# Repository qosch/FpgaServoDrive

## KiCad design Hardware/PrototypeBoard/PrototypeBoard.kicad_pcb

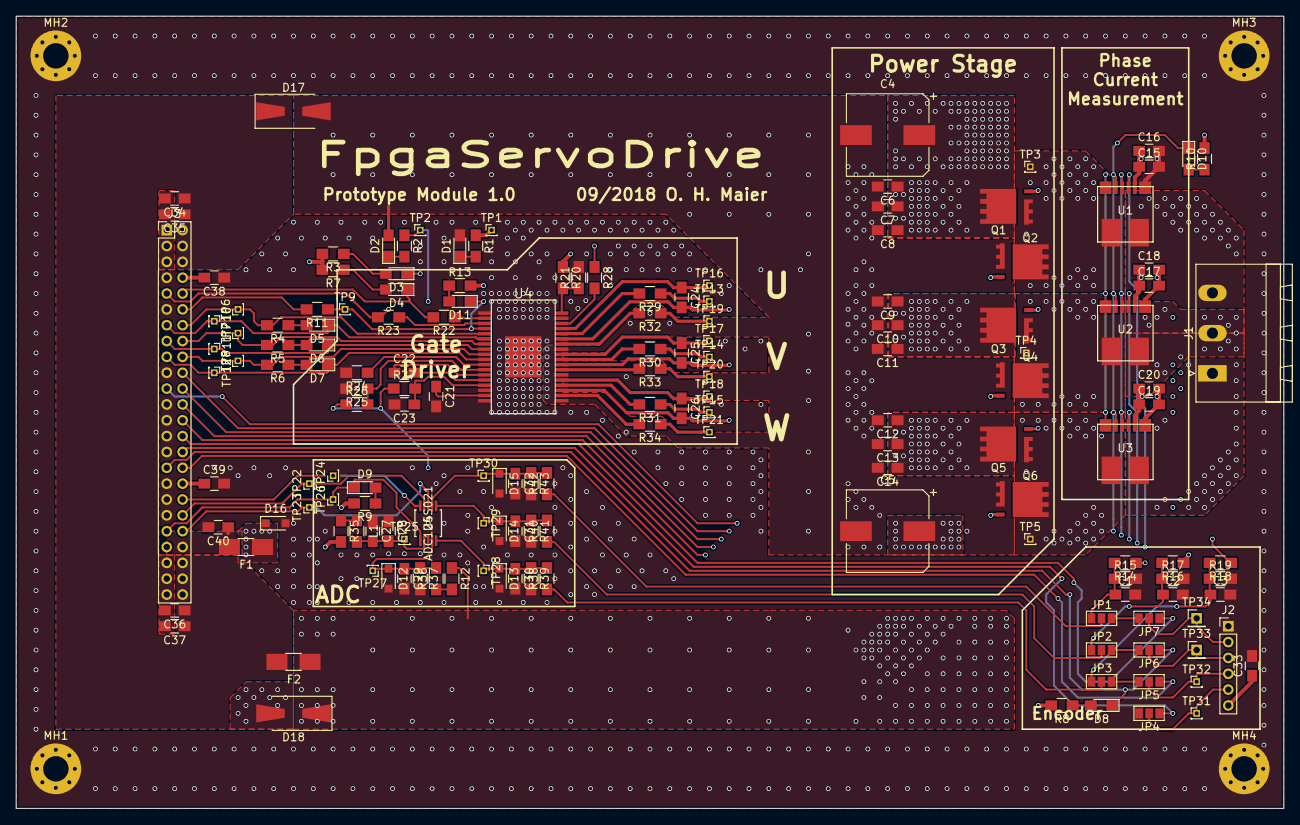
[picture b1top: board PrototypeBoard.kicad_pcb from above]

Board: 4 copper layers, 160.0 x 100.0 mm, 163 parts (0 on the bottom side), 91 nets.

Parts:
C1, C2, C3, C6, C8, C9, C11, C12, C14, C15, C17, C19, C28, C29, C33, C35, C36, C38, C39, C40: 100n; C_0805_HandSoldering
C4, C5: 220μF, 50V; CP_Elec_10x10
C7, C10, C13: 4.7μ, 50V; C_0805_HandSoldering
C16, C18, C20, C27: 1μ; C_0805_HandSoldering
C21, C23: 2,2µ; C_0805_HandSoldering
C22, C24, C25, C26: 1µ; C_0805_HandSoldering
C30, C31, C32: DNP; C_0805_HandSoldering
C34, C37: 4.7μ; C_0805_HandSoldering
D1: 3.3V; LED_0805_HandSoldering
D2: 5.5-28V; LED_0805_HandSoldering
D3, D4, D11: Red; LED_0805_HandSoldering
D5, D6, D7, D8, D9, D10: Yellow; LED_0805_HandSoldering
D12, D13, D14, D15: 3.3V; D_SOD-323_HandSoldering
D16: 3.5V; D_SOD-323_HandSoldering
D17, D18: 30V; D_SMA-SMB_Universal_Handsoldering
F1: 200mA; Fuse_SMD1206_HandSoldering
F2: 3A; Fuse_SMD1206_HandSoldering
J1: Conn_01x03; PhoenixContact_MSTBA-G_03x5.08mm_Angled
J2: Conn_01x06; Pin_Header_Straight_1x06_Pitch2.00mm
J3: ControlSupplyConnector; Pin_Header_Straight_2x24_Pitch2.00mm
JP1, JP2, JP3: Hall/Phase; GS3
JP4, JP5, JP6, JP7: SPI/Hall; GS3
L1: 1μ; L_0805_HandSoldering
MH1, MH2, MH3, MH4: MountingHole_Pad; MountingHole_3.2mm_M3_Pad_Via
Q1, Q2, Q3, Q4, Q5, Q6: Q_NMOS_SGD; TDSON-8_FL
R1, R3, R7, R13: 220; R_0805_HandSoldering
R2, R38, R40, R42: 6.8k; R_0805_HandSoldering
R4, R5, R6, R8, R9, R10: 560; R_0805_HandSoldering
R11, R21: 10k; R_0805_HandSoldering
R12, R24, R35: 0; R_0805_HandSoldering
R14, R16, R18: 1.5k; R_0805_HandSoldering
R15, R17, R19, R43: DNP; R_0805_HandSoldering
R20: 63k; R_0805_HandSoldering
R22, R23, R26: 5k; R_0805_HandSoldering
R25: 47k; R_0805_HandSoldering
R27: 4.7; R_0805_HandSoldering
R28, R37, R39, R41: 1k; R_0805_HandSoldering
R29, R30, R31, R32, R33, R34: 10; R_0805_HandSoldering
R36: 8.2k; R_0805_HandSoldering
TP1: 3.3V; Pin_Header_Straight_1x01_Pitch1.00mm
TP2: 5.5-28V; Pin_Header_Straight_1x01_Pitch1.00mm
TP3: PhaseU; Pin_Header_Straight_1x01_Pitch1.00mm
TP4: PhaseV; Pin_Header_Straight_1x01_Pitch1.00mm
TP5: PhaseW; Pin_Header_Straight_1x01_Pitch1.00mm
TP6: ~PwmUH; Pin_Header_Straight_1x01_Pitch1.00mm
TP7: ~PwmVH; Pin_Header_Straight_1x01_Pitch1.00mm
TP8: ~PwmWH; Pin_Header_Straight_1x01_Pitch1.00mm
TP9: GdEna; Pin_Header_Straight_1x01_Pitch1.00mm
TP10: PwmUL; Pin_Header_Straight_1x01_Pitch1.00mm
TP11: PwmVL; Pin_Header_Straight_1x01_Pitch1.00mm
TP12: PwmWL; Pin_Header_Straight_1x01_Pitch1.00mm
TP13: GateUH; Pin_Header_Straight_1x01_Pitch1.00mm
TP14: GateVH; Pin_Header_Straight_1x01_Pitch1.00mm
TP15: GateWH; Pin_Header_Straight_1x01_Pitch1.00mm
TP16: BstU; Pin_Header_Straight_1x01_Pitch1.00mm
TP17: BstV; Pin_Header_Straight_1x01_Pitch1.00mm
TP18: BstW; Pin_Header_Straight_1x01_Pitch1.00mm
TP19: GateUL; Pin_Header_Straight_1x01_Pitch1.00mm
TP20: GateVL; Pin_Header_Straight_1x01_Pitch1.00mm
TP21: GateWL; Pin_Header_Straight_1x01_Pitch1.00mm
TP22: AdcMiso; Pin_Header_Straight_1x01_Pitch1.00mm
TP23: AdcMosi; Pin_Header_Straight_1x01_Pitch1.00mm
TP24: AdcSclk; Pin_Header_Straight_1x01_Pitch1.00mm
TP25: AdcV; Pin_Header_Straight_1x01_Pitch1.00mm
TP26: ~AdcCs; Pin_Header_Straight_1x01_Pitch1.00mm
TP27: Adc4; Pin_Header_Straight_1x01_Pitch1.00mm
TP28: Adc3; Pin_Header_Straight_1x01_Pitch1.00mm
TP29: Adc2; Pin_Header_Straight_1x01_Pitch1.00mm
TP30: Adc1; Pin_Header_Straight_1x01_Pitch1.00mm
TP31: !EncCs/HallB; Pin_Header_Straight_1x01_Pitch1.00mm
TP32: EncMiso/HallC; Pin_Header_Straight_1x01_Pitch1.00mm
TP33: EncSclk/HallA; Pin_Header_Straight_1x01_Pitch2.00mm
TP34: EncMosi/NC; Pin_Header_Straight_1x01_Pitch2.00mm
U1, U2, U3: TLI4970-D025T4; PG-TISON-8-1
U4: TLE7185-1E; PG-DSO-36-38
U5: ADC124S021; ADC124S021CIMMXNOPB

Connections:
+3V3: C15.1, C16.1, C17.1, C18.1, C19.1, C20.1, C33.1, D16.1, F1.1, J2.6, R1.1, R3.2, R7.2, R8.2, R9.2, R10.2, R13.2, R20.1, R35.2, TP1.1, U1.2, U2.2, U3.2
+BATT: C4.1, C5.1, C6.1, C7.1, C8.1, C9.1, C10.1, C11.1, C12.1, C13.1, C14.1, D18.1, F2.1, Q1.3, Q3.3, Q5.3, R2.1, R12.1, R26.1, R27.1, R28.1, TP2.1
/MainConnector/3V3in: C38.2, C39.1, C40.1, F1.2, J3.8, J3.34, J3.42
/MainConnector/AdcSpiMiso: J3.38, TP22.1, U5.9
/MainConnector/AdcSpiMosi: J3.40, TP23.1, U5.8
/MainConnector/AdcSpiSclk: J3.36, TP24.1, U5.10
/MainConnector/CurrentSensSpiDoutU: J3.26, U1.3
/MainConnector/CurrentSensSpiDoutV: J3.24, U2.3
/MainConnector/CurrentSensSpiDoutW: J3.22, U3.3
/MainConnector/CurrentSensSpiSclk: J3.20, U1.4, U2.4, U3.4
/MainConnector/EncoderSpiMiso: J3.30, JP4.3
/MainConnector/EncoderSpiMosi: J3.32, JP5.3
/MainConnector/EncoderSpiSclk: J3.28, JP7.3
/MainConnector/GateDriverEna: J3.12, R11.2
/MainConnector/PowerIn: C34.1, C35.1, C36.1, C37.1, D17.1, F2.2, J3.2, J3.4, J3.6, J3.44, J3.46, J3.48
/MainConnector/PwmUL: D5.1, J3.13, TP10.1, U4.6
/MainConnector/PwmVL: D6.1, J3.15, TP11.1, U4.8
/MainConnector/PwmWL: D7.1, J3.17, TP12.1, U4.10
/MainConnector/~AdcSpiCs: D9.1, J3.39, TP26.1, U5.1
/MainConnector/~CurrentSensSpiCs: D10.1, J3.21, U1.5, U2.5, U3.5
/MainConnector/~EncoderSpiCs: D8.1, J3.31, JP6.3
/MainConnector/~GateDriverErr1: D3.1, J3.9, R23.2
/MainConnector/~GateDriverErr2: D4.1, J3.10, R22.2
/MainConnector/~PwmUH: J3.14, R4.2, TP6.1, U4.5
/MainConnector/~PwmVH: J3.16, R5.2, TP7.1, U4.7
/MainConnector/~PwmWH: J3.18, R6.2, TP8.1, U4.9
/MotorModule/Adc/ADC_IN1: JP1.2, R42.1
/MotorModule/Adc/ADC_IN2: JP2.2, R40.1
/MotorModule/Adc/ADC_IN3: JP3.2, R38.1
/MotorModule/Adc/ADC_IN4: R12.2, R36.1
/MotorModule/CurrentSensing/Power_Phase_U: C24.2, Q1.1, Q2.3, TP3.1, U1.7, U4.31
/MotorModule/CurrentSensing/Power_Phase_U_measured: J1.3, R14.1, U1.8
/MotorModule/CurrentSensing/Power_Phase_V: C25.2, Q3.1, Q4.3, TP4.1, U2.7, U4.26
/MotorModule/CurrentSensing/Power_Phase_V_measured: J1.2, R16.1, U2.8
/MotorModule/CurrentSensing/Power_Phase_W: C26.2, Q5.1, Q6.3, TP5.1, U3.7, U4.21
/MotorModule/CurrentSensing/Power_Phase_W_measured: J1.1, R18.1, U3.8
/MotorModule/EncoderConnector/HALL_A: JP1.1, JP7.1
/MotorModule/EncoderConnector/HALL_B: JP2.1, JP6.1
/MotorModule/EncoderConnector/HALL_C: JP3.1, JP5.1
/MotorModule/GateDriver/Gate_U_H: Q1.2, R29.1, TP13.1
/MotorModule/GateDriver/Gate_U_H_bR: R29.2, U4.32
/MotorModule/GateDriver/Gate_U_L: Q2.2, R32.1, TP19.1
/MotorModule/GateDriver/Gate_U_L_bR: R32.2, U4.30
/MotorModule/GateDriver/Gate_V_H: Q3.2, R30.1, TP14.1
/MotorModule/GateDriver/Gate_V_H_bR: R30.2, U4.27
/MotorModule/GateDriver/Gate_V_L: Q4.2, R33.1, TP20.1
/MotorModule/GateDriver/Gate_V_L_bR: R33.2, U4.25
/MotorModule/GateDriver/Gate_W_H: Q5.2, R31.1, TP15.1
/MotorModule/GateDriver/Gate_W_H_bR: R31.2, U4.22
/MotorModule/GateDriver/Gate_W_L: Q6.2, R34.1, TP21.1
/MotorModule/GateDriver/Gate_W_L_bR: R34.2, U4.20
/MotorModule/GateDriver/Logic_GD_ENA: D11.1, R11.1, TP9.1, U1.6, U2.6, U3.6, U4.4
GND: C1.2, C2.2, C3.2, C15.2, C16.2, C17.2, C18.2, C19.2, C20.2, C21.2, C23.2, C27.1, C28.1, C29.2, C30.2, C31.2, C32.2, C33.2, C38.1, C39.2, C40.2, D1.2, D12.2, D13.2, D14.2, D15.2, D16.2, J2.1, J3.7, J3.11, J3.19, J3.23, J3.25, J3.27, J3.29, J3.33, J3.35, J3.37, J3.41, JP4.1, MH1.1, MH2.1, MH3.1, MH4.1, R15.2, R17.2, R19.2, R21.2, R24.2, R25.2, R37.2, R39.2, R41.2, R43.2, U1.1, U2.1, U3.1, U4.1, U4.16, U4.18, U4.35, U4.37, U5.3
GNDPWR: C4.2, C5.2, C6.2, C7.2, C8.2, C9.2, C10.2, C11.2, C12.2, C13.2, C14.2, C34.2, C35.2, C36.2, C37.2, D2.2, D17.2, D18.2, J3.1, J3.3, J3.5, J3.43, J3.45, J3.47, Q2.1, Q4.1, Q6.1, U4.19, U4.24, U4.29
unnamed: C1.1, JP1.3, R14.2, R15.1
unnamed: C2.1, JP2.3, R16.2, R17.1
unnamed: C3.1, JP3.3, R18.2, R19.1
unnamed: C21.1, U4.17
unnamed: C22.1, U4.13
unnamed: C22.2, U4.14
unnamed: C23.1, R27.2, U4.15
unnamed: C24.1, TP16.1, U4.33
unnamed: C25.1, TP17.1, U4.28
unnamed: C26.1, TP18.1, U4.23
unnamed: C27.2, C28.2, L1.2, TP25.1, U5.2
unnamed: C29.1, D12.1, R36.2, R37.1, TP27.1, U5.4
unnamed: C30.1, D13.1, R38.2, R39.1, TP28.1, U5.5
unnamed: C31.1, D14.1, R40.2, R41.1, TP29.1, U5.6
unnamed: C32.1, D15.1, R42.2, R43.1, TP30.1, U5.7
unnamed: D1.1, R1.2
unnamed: D2.1, R2.2
unnamed: D3.2, R3.1
unnamed: D4.2, R7.1
unnamed: D5.2, R4.1
unnamed: D6.2, R5.1
unnamed: D7.2, R6.1
unnamed: D8.2, R8.1
unnamed: D9.2, R9.1
unnamed: D10.2, R10.1
unnamed: D11.2, R13.1
unnamed: J2.2, JP7.2, TP34.1
unnamed: J2.3, JP6.2, TP33.1
unnamed: J2.4, JP5.2, TP32.1
unnamed: J2.5, JP4.2, TP31.1
unnamed: L1.1, R35.1
unnamed: R20.2, R21.1, U4.36
unnamed: R22.1, U4.2
unnamed: R23.1, U4.3
unnamed: R24.1, U4.11
unnamed: R25.1, R26.2, U4.12
unnamed: R28.2, U4.34

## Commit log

2018-05-18 Initial commit, schematics mostly finished
2018-05-18 Fixed all ERC errors. Added power consumption estimation and other comments. Added links to datasheets. Dimensioned low pass and voltage dividers. Added TVS diodes for protection of voltage rails and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
2018-05-18 Assigned footprints (some of them might still be incorrect). Added relative path to footprints. Generated Netlist.
2018-05-18 forgot files
2018-05-25 generated board file
2018-05-28 Added footprint for power MOSFETs
2018-05-29 Corrected paste layer of footprints, deleted unnecessary files
2018-05-29 started layout
2018-05-30 some more layout work
2018-05-31 assigned net classes and a few net names
2018-06-01 minor progress in layout
2018-06-13 some more layout...
2018-06-15 more layout and some changes to schematic
2018-06-18 More Layout...
2018-06-22 layout and some pin swapping...
2018-08-21 First few line of FPGA gateware
2018-08-24 Migrated to kicad 5
2018-08-29 Layout almost done
2018-08-31 New, much bigger pcb layout, changes to connection PGND <-> GND
2018-08-31 continued to work on new layout
2018-09-02 New layout almost complete
2018-09-03 Gate driver closer to power stage, ground and power ground seperated completely, power ground traces to gate driver replaced by power planes, phase outputs now span across all layers (vias not places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
2018-09-06 Added LEDs for PWM, SPI communication, Gate Driver Errors and Gate Driver disabled
2018-09-07 All tracks routed, fixed bug in schematic, smaller test points
2019-01-08 Some deduplication, renaming and cleanups in the schematic

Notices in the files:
parts and their libraries:
Copyright 2016 Accelerated Designs. All rights reserved.
